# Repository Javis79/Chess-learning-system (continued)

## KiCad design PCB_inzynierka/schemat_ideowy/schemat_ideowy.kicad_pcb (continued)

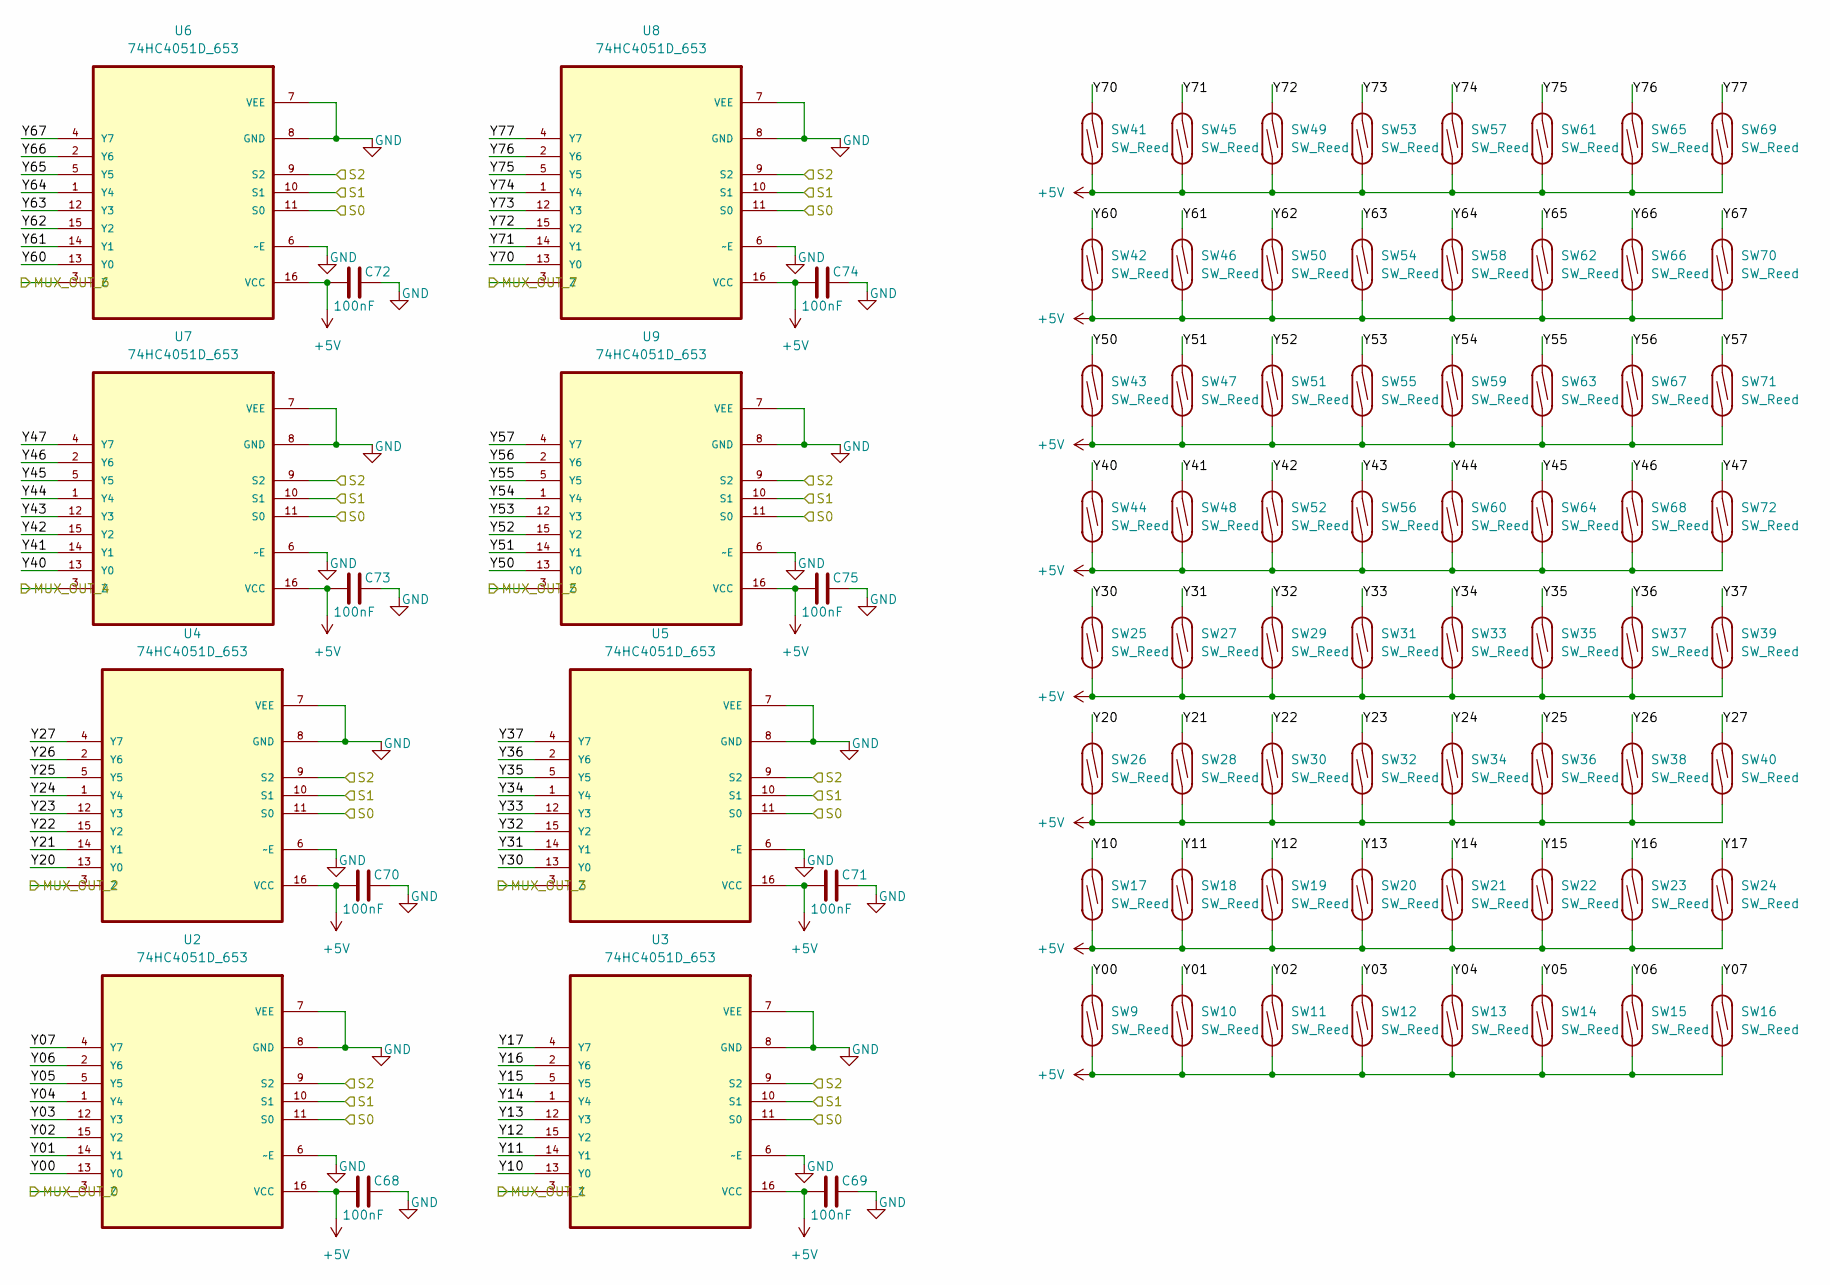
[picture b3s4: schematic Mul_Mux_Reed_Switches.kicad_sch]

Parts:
C68, C69, C70, C71, C72, C73, C74, C75: 100nF; C_0805_2012Metric_Pad1.18x1.45mm_HandSolder
SW9, SW10, SW11, SW12, SW13, SW14, SW15, SW16, SW17, SW18, SW19, SW20, SW21, SW22, SW23, SW24, SW25, SW26, SW27, SW28, SW29, SW30, SW31, SW32, SW33, SW34, SW35, SW36, SW37, SW38, SW39, SW40, SW41, SW42, SW43, SW44, SW45, SW46, SW47, SW48, SW49, SW50, SW51, SW52, SW53, SW54, SW55, SW56, SW57, SW58, SW59, SW60, SW61, SW62, SW63, SW64, SW65, SW66, SW67, SW68, SW69, SW70, SW71, SW72: SW_Reed; ReedSwitch_2x14mm
U2, U3, U4, U5, U6, U7, U8, U9: 74HC4051D_653; SOIC127P600X175-16N; MPN 74HC4051D,653

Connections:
+5V: C68.1, C69.1, C70.1, C71.1, C72.1, C73.1, C74.1, C75.1, SW9.2, SW10.2, SW11.2, SW12.2, SW13.2, SW14.2, SW15.2, SW16.2, SW17.2, SW18.2, SW19.2, SW20.2, SW21.2, SW22.2, SW23.2, SW24.2, SW25.2, SW26.2, SW27.2, SW28.2, SW29.2, SW30.2, SW31.2, SW32.2, SW33.2, SW34.2, SW35.2, SW36.2, SW37.2, SW38.2, SW39.2, SW40.2, SW41.2, SW42.2, SW43.2, SW44.2, SW45.2, SW46.2, SW47.2, SW48.2, SW49.2, SW50.2, SW51.2, SW52.2, SW53.2, SW54.2, SW55.2, SW56.2, SW57.2, SW58.2, SW59.2, SW60.2, SW61.2, SW62.2, SW63.2, SW64.2, SW65.2, SW66.2, SW67.2, SW68.2, SW69.2, SW70.2, SW71.2, SW72.2, U2.16 (VCC), U3.16 (VCC), U4.16 (VCC), U5.16 (VCC), U6.16 (VCC), U7.16 (VCC), U8.16 (VCC), U9.16 (VCC); also elsewhere on the board
/MUX_OUT_0: U2.3 (Z); also elsewhere on the board
/MUX_OUT_1: U3.3 (Z); also elsewhere on the board
/MUX_OUT_2: U4.3 (Z); also elsewhere on the board
/MUX_OUT_3: U5.3 (Z); also elsewhere on the board
/MUX_OUT_4: U7.3 (Z); also elsewhere on the board
/MUX_OUT_5: U9.3 (Z); also elsewhere on the board
/MUX_OUT_6: U6.3 (Z); also elsewhere on the board
/MUX_OUT_7: U8.3 (Z); also elsewhere on the board
/Mul_Mux_Reed_Switches/Y00: SW9.1, U2.13 (Y0)
/Mul_Mux_Reed_Switches/Y01: SW10.1, U2.14 (Y1)
/Mul_Mux_Reed_Switches/Y02: SW11.1, U2.15 (Y2)
/Mul_Mux_Reed_Switches/Y03: SW12.1, U2.12 (Y3)
/Mul_Mux_Reed_Switches/Y04: SW13.1, U2.1 (Y4)
/Mul_Mux_Reed_Switches/Y05: SW14.1, U2.5 (Y5)
/Mul_Mux_Reed_Switches/Y06: SW15.1, U2.2 (Y6)
/Mul_Mux_Reed_Switches/Y07: SW16.1, U2.4 (Y7)
/Mul_Mux_Reed_Switches/Y10: SW17.1, U3.13 (Y0)
/Mul_Mux_Reed_Switches/Y11: SW18.1, U3.14 (Y1)
/Mul_Mux_Reed_Switches/Y12: SW19.1, U3.15 (Y2)
/Mul_Mux_Reed_Switches/Y13: SW20.1, U3.12 (Y3)
/Mul_Mux_Reed_Switches/Y14: SW21.1, U3.1 (Y4)
/Mul_Mux_Reed_Switches/Y15: SW22.1, U3.5 (Y5)
/Mul_Mux_Reed_Switches/Y16: SW23.1, U3.2 (Y6)
/Mul_Mux_Reed_Switches/Y17: SW24.1, U3.4 (Y7)
/Mul_Mux_Reed_Switches/Y20: SW26.1, U4.13 (Y0)
/Mul_Mux_Reed_Switches/Y21: SW28.1, U4.14 (Y1)
/Mul_Mux_Reed_Switches/Y22: SW30.1, U4.15 (Y2)
/Mul_Mux_Reed_Switches/Y23: SW32.1, U4.12 (Y3)
/Mul_Mux_Reed_Switches/Y24: SW34.1, U4.1 (Y4)
/Mul_Mux_Reed_Switches/Y25: SW36.1, U4.5 (Y5)
/Mul_Mux_Reed_Switches/Y26: SW38.1, U4.2 (Y6)
/Mul_Mux_Reed_Switches/Y27: SW40.1, U4.4 (Y7)
/Mul_Mux_Reed_Switches/Y30: SW25.1, U5.13 (Y0)
/Mul_Mux_Reed_Switches/Y31: SW27.1, U5.14 (Y1)
/Mul_Mux_Reed_Switches/Y32: SW29.1, U5.15 (Y2)
/Mul_Mux_Reed_Switches/Y33: SW31.1, U5.12 (Y3)
/Mul_Mux_Reed_Switches/Y34: SW33.1, U5.1 (Y4)
/Mul_Mux_Reed_Switches/Y35: SW35.1, U5.5 (Y5)
/Mul_Mux_Reed_Switches/Y36: SW37.1, U5.2 (Y6)
/Mul_Mux_Reed_Switches/Y37: SW39.1, U5.4 (Y7)
/Mul_Mux_Reed_Switches/Y40: SW44.1, U7.13 (Y0)
/Mul_Mux_Reed_Switches/Y41: SW48.1, U7.14 (Y1)
/Mul_Mux_Reed_Switches/Y42: SW52.1, U7.15 (Y2)
/Mul_Mux_Reed_Switches/Y43: SW56.1, U7.12 (Y3)
/Mul_Mux_Reed_Switches/Y44: SW60.1, U7.1 (Y4)
/Mul_Mux_Reed_Switches/Y45: SW64.1, U7.5 (Y5)
/Mul_Mux_Reed_Switches/Y46: SW68.1, U7.2 (Y6)
/Mul_Mux_Reed_Switches/Y47: SW72.1, U7.4 (Y7)
/Mul_Mux_Reed_Switches/Y50: SW43.1, U9.13 (Y0)
/Mul_Mux_Reed_Switches/Y51: SW47.1, U9.14 (Y1)
/Mul_Mux_Reed_Switches/Y52: SW51.1, U9.15 (Y2)
/Mul_Mux_Reed_Switches/Y53: SW55.1, U9.12 (Y3)
/Mul_Mux_Reed_Switches/Y54: SW59.1, U9.1 (Y4)
/Mul_Mux_Reed_Switches/Y55: SW63.1, U9.5 (Y5)
/Mul_Mux_Reed_Switches/Y56: SW67.1, U9.2 (Y6)
/Mul_Mux_Reed_Switches/Y57: SW71.1, U9.4 (Y7)
/Mul_Mux_Reed_Switches/Y60: SW42.1, U6.13 (Y0)
/Mul_Mux_Reed_Switches/Y61: SW46.1, U6.14 (Y1)
/Mul_Mux_Reed_Switches/Y62: SW50.1, U6.15 (Y2)
/Mul_Mux_Reed_Switches/Y63: SW54.1, U6.12 (Y3)
/Mul_Mux_Reed_Switches/Y64: SW58.1, U6.1 (Y4)
/Mul_Mux_Reed_Switches/Y65: SW62.1, U6.5 (Y5)
/Mul_Mux_Reed_Switches/Y66: SW66.1, U6.2 (Y6)
/Mul_Mux_Reed_Switches/Y67: SW70.1, U6.4 (Y7)
/Mul_Mux_Reed_Switches/Y70: SW41.1, U8.13 (Y0)
/Mul_Mux_Reed_Switches/Y71: SW45.1, U8.14 (Y1)
/Mul_Mux_Reed_Switches/Y72: SW49.1, U8.15 (Y2)
/Mul_Mux_Reed_Switches/Y73: SW53.1, U8.12 (Y3)
/Mul_Mux_Reed_Switches/Y74: SW57.1, U8.1 (Y4)
/Mul_Mux_Reed_Switches/Y75: SW61.1, U8.5 (Y5)
/Mul_Mux_Reed_Switches/Y76: SW65.1, U8.2 (Y6)
/Mul_Mux_Reed_Switches/Y77: SW69.1, U8.4 (Y7)
/S0: U2.11 (S0), U3.11 (S0), U4.11 (S0), U5.11 (S0), U6.11 (S0), U7.11 (S0), U8.11 (S0), U9.11 (S0); also elsewhere on the board
/S1: U2.10 (S1), U3.10 (S1), U4.10 (S1), U5.10 (S1), U6.10 (S1), U7.10 (S1), U8.10 (S1), U9.10 (S1); also elsewhere on the board
/S2: U2.9 (S2), U3.9 (S2), U4.9 (S2), U5.9 (S2), U6.9 (S2), U7.9 (S2), U8.9 (S2), U9.9 (S2); also elsewhere on the board
GND: C68.2, C69.2, C70.2, C71.2, C72.2, C73.2, C74.2, C75.2, U2.6 (~E), U2.7 (VEE), U2.8 (GND), U3.6 (~E), U3.7 (VEE), U3.8 (GND), U4.6 (~E), U4.7 (VEE), U4.8 (GND), U5.6 (~E), U5.7 (VEE), U5.8 (GND), U6.6 (~E), U6.7 (VEE), U6.8 (GND), U7.6 (~E), U7.7 (VEE), U7.8 (GND), U8.6 (~E), U8.7 (VEE), U8.8 (GND), U9.6 (~E), U9.7 (VEE), U9.8 (GND); also elsewhere on the board

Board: 2 copper layers, 224 parts (0 on the bottom side), 159 nets, no tracks yet.

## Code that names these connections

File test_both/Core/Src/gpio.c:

/* USER CODE BEGIN Header */
/**
  ******************************************************************************
  * @file    gpio.c
  * @brief   This file provides code for the configuration
  *          of all used GPIO pins.
  ******************************************************************************
  * @attention
  *
  * Copyright (c) 2025 STMicroelectronics.
  * All rights reserved.
  *
  * This software is licensed under terms that can be found in the LICENSE file
  * in the root directory of this software component.
  * If no LICENSE file comes with this software, it is provided AS-IS.
  *
  ******************************************************************************
  */
/* USER CODE END Header */

/* Includes ------------------------------------------------------------------*/
#include "gpio.h"

/* USER CODE BEGIN 0 */

/* USER CODE END 0 */

/*----------------------------------------------------------------------------*/
/* Configure GPIO                                                             */
/*----------------------------------------------------------------------------*/
/* USER CODE BEGIN 1 */

/* USER CODE END 1 */

/** Configure pins as
        * Analog
        * Input
        * Output
        * EVENT_OUT
        * EXTI
*/
void MX_GPIO_Init(void)
{

	GPIO_InitTypeDef GPIO_InitStruct = {0};

	/* GPIO Ports Clock Enable */
	__HAL_RCC_GPIOC_CLK_ENABLE();
	__HAL_RCC_GPIOH_CLK_ENABLE();
	__HAL_RCC_GPIOA_CLK_ENABLE();
	__HAL_RCC_GPIOB_CLK_ENABLE();


	//SCREEN RESET
	HAL_GPIO_WritePin(GPIOC, GPIO_PIN_7, GPIO_PIN_RESET);
	//SCREEN DC
	HAL_GPIO_WritePin(GPIOA, GPIO_PIN_9, GPIO_PIN_RESET);
	//SCREEN CS
	HAL_GPIO_WritePin(GPIOB, GPIO_PIN_6, GPIO_PIN_RESET);

	/*Configure GPIO pin : B1_Pin */
	GPIO_InitStruct.Pin = B1_Pin;
	GPIO_InitStruct.Mode = GPIO_MODE_IT_FALLING;
	GPIO_InitStruct.Pull = GPIO_NOPULL;
	HAL_GPIO_Init(B1_GPIO_Port, &GPIO_InitStruct);

	/*Configure GPIO pin : PC7 */
	GPIO_InitStruct.Pin = GPIO_PIN_7;
	GPIO_InitStruct.Mode = GPIO_MODE_OUTPUT_PP;
	GPIO_InitStruct.Pull = GPIO_NOPULL;
	GPIO_InitStruct.Speed = GPIO_SPEED_FREQ_LOW;
	HAL_GPIO_Init(GPIOC, &GPIO_InitStruct);

	/*Configure GPIO pin : PA9 */
	GPIO_InitStruct.Pin = GPIO_PIN_9;
	GPIO_InitStruct.Mode = GPIO_MODE_OUTPUT_PP;
	GPIO_InitStruct.Pull = GPIO_NOPULL;
	GPIO_InitStruct.Speed = GPIO_SPEED_FREQ_LOW;
	HAL_GPIO_Init(GPIOA, &GPIO_InitStruct);

	/*Configure GPIO pin : PB6 */
	GPIO_InitStruct.Pin = GPIO_PIN_6;
	GPIO_InitStruct.Mode = GPIO_MODE_OUTPUT_PP;
	GPIO_InitStruct.Pull = GPIO_NOPULL;
	GPIO_InitStruct.Speed = GPIO_SPEED_FREQ_LOW;
	HAL_GPIO_Init(GPIOB, &GPIO_InitStruct);

	HAL_GPIO_WritePin(GPIOC, GPIO_PIN_0|GPIO_PIN_1, GPIO_PIN_RESET);

	/*Configure GPIO pin Output Level */
	HAL_GPIO_WritePin(GPIOB, GPIO_PIN_0, GPIO_PIN_RESET);

	/* Configure GPIO pins : PC0 PC1 as inputs (mux outputs) */
	GPIO_InitStruct.Pin = GPIO_PIN_0 | GPIO_PIN_1;
	GPIO_InitStruct.Mode = GPIO_MODE_INPUT;
	GPIO_InitStruct.Pull = GPIO_PULLDOWN;
	HAL_GPIO_Init(GPIOC, &GPIO_InitStruct);


	// BUTTONS
	// Konfiguracja pinów PA0, PA1, PA4, PB0 jako wejścia z wewnętrznymi rezystorami pull-up
	GPIO_InitStruct.Pin = GPIO_PIN_0 | GPIO_PIN_1 | GPIO_PIN_4;  // PA0, PA1, PA4
	GPIO_InitStruct.Mode = GPIO_MODE_INPUT;
	GPIO_InitStruct.Pull = GPIO_PULLUP;  // Pull-up
	HAL_GPIO_Init(GPIOA, &GPIO_InitStruct);
	GPIO_InitStruct.Pin = GPIO_PIN_0;  // PB0
	GPIO_InitStruct.Pull = GPIO_PULLUP;  // Pull-up
	HAL_GPIO_Init(GPIOB, &GPIO_InitStruct);

	//MUX SELECT PINS
	GPIO_InitStruct.Pin = GPIO_PIN_10 | GPIO_PIN_11 | GPIO_PIN_12; // PC10, PC11, PC12
	GPIO_InitStruct.Mode = GPIO_MODE_OUTPUT_PP;  // Tryb wyjścia push-pull
	GPIO_InitStruct.Pull = GPIO_NOPULL;          // Bez rezystorów pull-up/pull-down
	GPIO_InitStruct.Speed = GPIO_SPEED_FREQ_LOW; // Niska prędkość
	HAL_GPIO_Init(GPIOC, &GPIO_InitStruct);

	//SD CARD CS
	GPIO_InitStruct.Pin = GPIO_PIN_10;
	GPIO_InitStruct.Mode = GPIO_MODE_OUTPUT_PP;
	GPIO_InitStruct.Pull = GPIO_PULLUP;
	GPIO_InitStruct.Speed = GPIO_SPEED_FREQ_LOW;
	HAL_GPIO_Init(GPIOA, &GPIO_InitStruct);



}

/* USER CODE BEGIN 2 */

/* USER CODE END 2 */

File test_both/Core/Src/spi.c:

/* USER CODE BEGIN Header */
/**
  ******************************************************************************
  * @file    spi.c
  * @brief   This file provides code for the configuration
  *          of the SPI instances.
  ******************************************************************************
  * @attention
  *
  * Copyright (c) 2025 STMicroelectronics.
  * All rights reserved.
  *
  * This software is licensed under terms that can be found in the LICENSE file
  * in the root directory of this software component.
  * If no LICENSE file comes with this software, it is provided AS-IS.
  *
  ******************************************************************************
  */
/* USER CODE END Header */
/* Includes ------------------------------------------------------------------*/
#include "spi.h"

/* USER CODE BEGIN 0 */

/* USER CODE END 0 */
#define CS_TFT_GPIO_Port   GPIOB
#define CS_TFT_Pin         GPIO_PIN_6
#define DC_TFT_GPIO_Port   GPIOA
#define DC_TFT_Pin         GPIO_PIN_9
#define RST_TFT_GPIO_Port  GPIOC
#define RST_TFT_Pin        GPIO_PIN_7
#define CS_SD_GPIO_Port    GPIOA
#define CS_SD_Pin          GPIO_PIN_10

SPI_HandleTypeDef hspi1;
DMA_HandleTypeDef hdma_spi1_tx;

SPI_HandleTypeDef hspi2;
DMA_HandleTypeDef hdma_spi2_tx;

/* SPI1 init function */
void MX_SPI1_Init(void)
{

  /* USER CODE BEGIN SPI1_Init 0 */

  /* USER CODE END SPI1_Init 0 */

  /* USER CODE BEGIN SPI1_Init 1 */

  /* USER CODE END SPI1_Init 1 */
  hspi1.Instance = SPI1;
  hspi1.Init.Mode = SPI_MODE_MASTER;
  hspi1.Init.Direction = SPI_DIRECTION_2LINES;
  hspi1.Init.DataSize = SPI_DATASIZE_8BIT;
  hspi1.Init.CLKPolarity = SPI_POLARITY_LOW;
  hspi1.Init.CLKPhase = SPI_PHASE_1EDGE;
  hspi1.Init.NSS = SPI_NSS_SOFT;
  hspi1.Init.BaudRatePrescaler = SPI_BAUDRATEPRESCALER_8;
  hspi1.Init.FirstBit = SPI_FIRSTBIT_MSB;
  hspi1.Init.TIMode = SPI_TIMODE_DISABLE;
  hspi1.Init.CRCCalculation = SPI_CRCCALCULATION_DISABLE;
  hspi1.Init.CRCPolynomial = 10;
  if (HAL_SPI_Init(&hspi1) != HAL_OK)
  {
    Error_Handler();
  }
  /* USER CODE BEGIN SPI1_Init 2 */

  /* USER CODE END SPI1_Init 2 */

}

void MX_SPI2_Init(void)
{

  /* USER CODE BEGIN SPI2_Init 0 */

  /* USER CODE END SPI2_Init 0 */

  /* USER CODE BEGIN SPI2_Init 1 */

  /* USER CODE END SPI2_Init 1 */
  hspi2.Instance = SPI2;
  hspi2.Init.Mode = SPI_MODE_MASTER;
  hspi2.Init.Direction = SPI_DIRECTION_2LINES;
  hspi2.Init.DataSize = SPI_DATASIZE_8BIT;
  hspi2.Init.CLKPolarity = SPI_POLARITY_LOW;
  hspi2.Init.CLKPhase = SPI_PHASE_1EDGE;
  hspi2.Init.NSS = SPI_NSS_SOFT;
  hspi2.Init.BaudRatePrescaler = SPI_BAUDRATEPRESCALER_256;
  hspi2.Init.FirstBit = SPI_FIRSTBIT_MSB;
  hspi2.Init.TIMode = SPI_TIMODE_DISABLE;
  hspi2.Init.CRCCalculation = SPI_CRCCALCULATION_DISABLE;
  hspi2.Init.CRCPolynomial = 10;
  if (HAL_SPI_Init(&hspi2) != HAL_OK)
  {
    Error_Handler();
  }
  /* USER CODE BEGIN SPI2_Init 2 */

  /* USER CODE END SPI2_Init 2 */

}


void HAL_SPI_MspInit(SPI_HandleTypeDef* spiHandle)
{

  GPIO_InitTypeDef GPIO_InitStruct = {0};
  if(spiHandle->Instance==SPI1)
  {
  /* USER CODE BEGIN SPI1_MspInit 0 */

  /* USER CODE END SPI1_MspInit 0 */
    /* SPI1 clock enable */
    __HAL_RCC_SPI1_CLK_ENABLE();

    __HAL_RCC_GPIOA_CLK_ENABLE();
    /**SPI1 GPIO Configuration
    PA5     ------> SPI1_SCK
    PA6     ------> SPI1_MISO
    PA7     ------> SPI1_MOSI
    */
    GPIO_InitStruct.Pin = GPIO_PIN_5|GPIO_PIN_6|GPIO_PIN_7;
    GPIO_InitStruct.Mode = GPIO_MODE_AF_PP;
    GPIO_InitStruct.Pull = GPIO_NOPULL;
    GPIO_InitStruct.Speed = GPIO_SPEED_FREQ_VERY_HIGH;
    GPIO_InitStruct.Alternate = GPIO_AF5_SPI1;
    HAL_GPIO_Init(GPIOA, &GPIO_InitStruct);

    /* SPI1 DMA Init */
    /* SPI1_TX Init */
    hdma_spi1_tx.Instance = DMA2_Stream3;
    hdma_spi1_tx.Init.Channel = DMA_CHANNEL_3;
    hdma_spi1_tx.Init.Direction = DMA_MEMORY_TO_PERIPH;
    hdma_spi1_tx.Init.PeriphInc = DMA_PINC_DISABLE;
    hdma_spi1_tx.Init.MemInc = DMA_MINC_ENABLE;
    hdma_spi1_tx.Init.PeriphDataAlignment = DMA_PDATAALIGN_BYTE;
    hdma_spi1_tx.Init.MemDataAlignment = DMA_MDATAALIGN_BYTE;
    hdma_spi1_tx.Init.Mode = DMA_NORMAL;
    hdma_spi1_tx.Init.Priority = DMA_PRIORITY_LOW;
    hdma_spi1_tx.Init.FIFOMode = DMA_FIFOMODE_DISABLE;
    if (HAL_DMA_Init(&hdma_spi1_tx) != HAL_OK)
    {
      Error_Handler();
    }

    __HAL_LINKDMA(spiHandle,hdmatx,hdma_spi1_tx);

  /* USER CODE BEGIN SPI1_MspInit 1 */

  /* USER CODE END SPI1_MspInit 1 */
  }

  if(spiHandle->Instance==SPI2)
   {
   /* USER CODE BEGIN SPI2_MspInit 0 */

   /* USER CODE END SPI2_MspInit 0 */
     /* SPI2 clock enable */
     __HAL_RCC_SPI2_CLK_ENABLE();

     __HAL_RCC_GPIOC_CLK_ENABLE();
     __HAL_RCC_GPIOB_CLK_ENABLE();
     /**SPI2 GPIO Configuration
     PC2     ------> SPI2_MISO
     PC3     ------> SPI2_MOSI
     PB10     ------> SPI2_SCK
     */
     GPIO_InitStruct.Pin = GPIO_PIN_2|GPIO_PIN_3;
     GPIO_InitStruct.Mode = GPIO_MODE_AF_PP;
     GPIO_InitStruct.Pull = GPIO_NOPULL;
     GPIO_InitStruct.Speed = GPIO_SPEED_FREQ_VERY_HIGH;
     GPIO_InitStruct.Alternate = GPIO_AF5_SPI2;
     HAL_GPIO_Init(GPIOC, &GPIO_InitStruct);

     GPIO_InitStruct.Pin = GPIO_PIN_10;
     GPIO_InitStruct.Mode = GPIO_MODE_AF_PP;
     GPIO_InitStruct.Pull = GPIO_NOPULL;
     GPIO_InitStruct.Speed = GPIO_SPEED_FREQ_VERY_HIGH;
     GPIO_InitStruct.Alternate = GPIO_AF5_SPI2;
     HAL_GPIO_Init(GPIOB, &GPIO_InitStruct);

     /* SPI2 DMA Init */
     /* SPI2_TX Init */
     hdma_spi2_tx.Instance = DMA1_Stream4;
     hdma_spi2_tx.Init.Channel = DMA_CHANNEL_0;
     hdma_spi2_tx.Init.Direction = DMA_MEMORY_TO_PERIPH;
     hdma_spi2_tx.Init.PeriphInc = DMA_PINC_DISABLE;
     hdma_spi2_tx.Init.MemInc = DMA_MINC_ENABLE;
     hdma_spi2_tx.Init.PeriphDataAlignment = DMA_PDATAALIGN_BYTE;
     hdma_spi2_tx.Init.MemDataAlignment = DMA_MDATAALIGN_BYTE;
     hdma_spi2_tx.Init.Mode = DMA_NORMAL;
     hdma_spi2_tx.Init.Priority = DMA_PRIORITY_LOW;
     hdma_spi2_tx.Init.FIFOMode = DMA_FIFOMODE_DISABLE;
     if (HAL_DMA_Init(&hdma_spi2_tx) != HAL_OK)
     {
       Error_Handler();
     }

     __HAL_LINKDMA(spiHandle,hdmatx,hdma_spi2_tx);

   /* USER CODE BEGIN SPI2_MspInit 1 */

   /* USER CODE END SPI2_MspInit 1 */
   }

}

void HAL_SPI_MspDeInit(SPI_HandleTypeDef* spiHandle)
{

  if(spiHandle->Instance==SPI1)
  {
  /* USER CODE BEGIN SPI1_MspDeInit 0 */

  /* USER CODE END SPI1_MspDeInit 0 */
    /* Peripheral clock disable */
    __HAL_RCC_SPI1_CLK_DISABLE();

    /**SPI1 GPIO Configuration
    PA5     ------> SPI1_SCK
    PA6     ------> SPI1_MISO
    PA7     ------> SPI1_MOSI
    */
    HAL_GPIO_DeInit(GPIOA, GPIO_PIN_5|GPIO_PIN_6|GPIO_PIN_7);

    /* SPI1 DMA DeInit */
    HAL_DMA_DeInit(spiHandle->hdmatx);
  /* USER CODE BEGIN SPI1_MspDeInit 1 */

  /* USER CODE END SPI1_MspDeInit 1 */
  }

  if(spiHandle->Instance==SPI2)
    {
    /* USER CODE BEGIN SPI2_MspDeInit 0 */

    /* USER CODE END SPI2_MspDeInit 0 */
      /* Peripheral clock disable */
      __HAL_RCC_SPI2_CLK_DISABLE();

      /**SPI2 GPIO Configuration
      PC2     ------> SPI2_MISO
      PC3     ------> SPI2_MOSI
      PB10     ------> SPI2_SCK
      */
      HAL_GPIO_DeInit(GPIOC, GPIO_PIN_2|GPIO_PIN_3);

      HAL_GPIO_DeInit(GPIOB, GPIO_PIN_10);

      /* SPI2 DMA DeInit */
      HAL_DMA_DeInit(spiHandle->hdmatx);
    /* USER CODE BEGIN SPI2_MspDeInit 1 */

    /* USER CODE END SPI2_MspDeInit 1 */
    }

}

/* USER CODE BEGIN 1 */

/* USER CODE END 1 */

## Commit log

2025-08-19 Add files via upload
    Napotkane problemy/techniczne aspekty o których chciałbym pamiętać przy pisaniu pracy
2025-10-10 Paczka z zespolonymi dzialajacymi dwoma ukladami, matryca led ARGB 8x8 oraz wyswietlacz lcd 2.8' wraz z przygotowanymi funkcjami do wyswietlania ruchu figur szachowych oraz przykladowemu zapisowi otw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
2025-11-03 rozbudowa menu, obsluga wykrywania ruchow
2025-11-04 Schemat ideowy, footprinty, przygotowania do PCB
2025-11-07 przygotowanie do tworzenia pcb 4x4 led matrix
2025-11-10 first version of 4x4 pcb for chessboard
2025-11-11 plytka 4x4 zawierajaca mux, reed switche i ledy argb v1.0
2025-11-13 obie plytki pcb przygotowane, schematy ideowe opisane
2025-11-17 pcb v1.0, przygotowane pliki do fabryki pcb, zamowienie zlozone, poprawa przelotek
2025-11-17 uporzadkowanie folderow, dodanie i wypelnienie BOM, zamowienie elementow
2025-11-18 pierwsze modele 3D, bez szachownicy sama podstawa na pcb
